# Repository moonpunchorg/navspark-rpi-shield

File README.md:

# NavSpark Shield for Raspberry Pi

[NavSpark][NavSpark] is Arduino compatible microcontroller board that has built in satellite navigation ([GPS][GPS] by default, and some models add [GLONASS][GLONASS], [BeiDou][BeiDou], etc...).

This adapter board provides means to connect the NavSpark board to a Raspberry Pi / Raspberry Pi 2.

For one example usecase, could create [a local network NTP server with accurate statellite timing through GPS+1PPS][timing]

## Files

This repository contains the design files using [KiCad 4.0][kicad]. The appropriate directories also contain the Gerber files, ready to be manufactured.

A note for those using [Seeed's FusionPCB service][fusionpcb]: the edge cuts filename needs to be changed from `*.gm1` to `*.gml`, and the drill file from `*.drl` to `.txt`.

## PCB

Revision v1, the proof of concept looks like this:

![PCB Front][pcbfront]

![PCB Back][pcbback]

[NavSpark]: http://www.navspark.com.tw/ "NavSpark homepage"
[GPS]: https://en.wikipedia.org/wiki/Global_Positioning_System "GPS on Wikipedia"
[GLONASS]: https://en.wikipedia.org/wiki/Global_Positioning_System "GLONASS on Wikipedia"
[BeiDou]: https://en.wikipedia.org/wiki/BeiDou_Navigation_Satellite_System "BeiDou on Wikipedia"
[timing]: https://gergely.imreh.net/blog/2015/11/navspark-beidou-ntp/ "Dual Satellite NTP server with Navspark"
[kicad]: http://kicad.org/ "KiCad homepage"
[fusionpcb]: https://www.seeedstudio.com/service/index.php?r=pcb "Seeed Studio FusionPCB"

[pcbfront]: ./images/navspark_rpi_shield_v1_front.png "PCB front rendering with Kicad"
[pcbback]: ./images/navspark_rpi_shield_v1_back.png "PCB back rendering with KiCad"

## License

Copyright 2015 Gergely Imreh <imrehg@gmail.com>

This documentation describes Open Hardware and is licensed under the
[CERN OHL v1.2](./LICENSE.txt).

You may redistribute and modify this documentation under the terms of the
CERN OHL v.1.2. (http://ohwr.org/cernohl). This documentation is distributed
WITHOUT ANY EXPRESS OR IMPLIED WARRANTY, INCLUDING OF MERCHANTABILITY,
SATISFACTORY QUALITY AND FITNESS FOR A PARTICULAR PURPOSE.
Please see the CERN OHL v.1.2 for applicable conditions.

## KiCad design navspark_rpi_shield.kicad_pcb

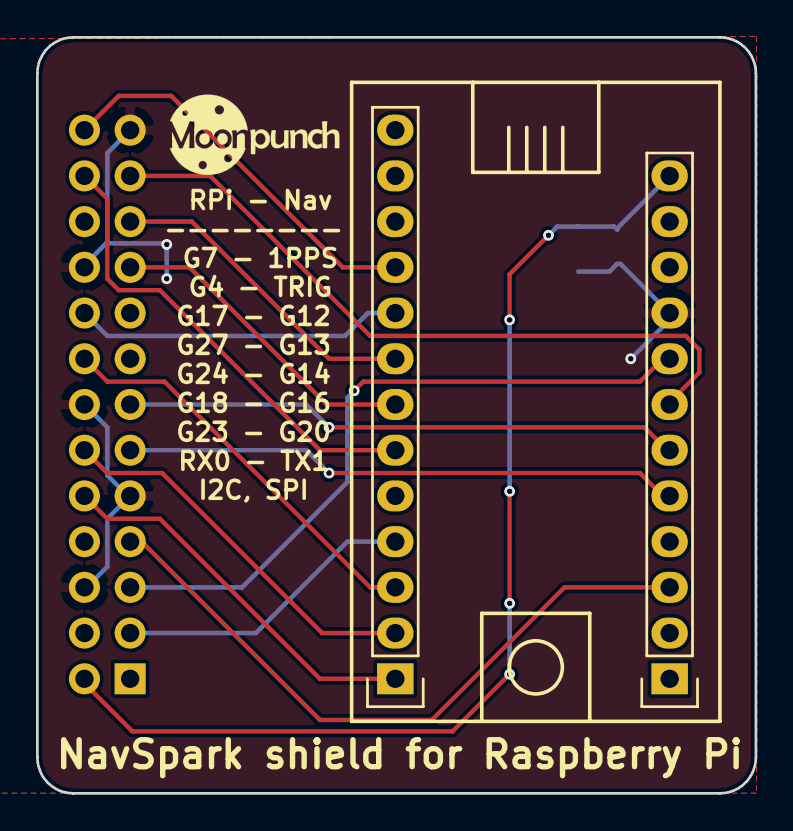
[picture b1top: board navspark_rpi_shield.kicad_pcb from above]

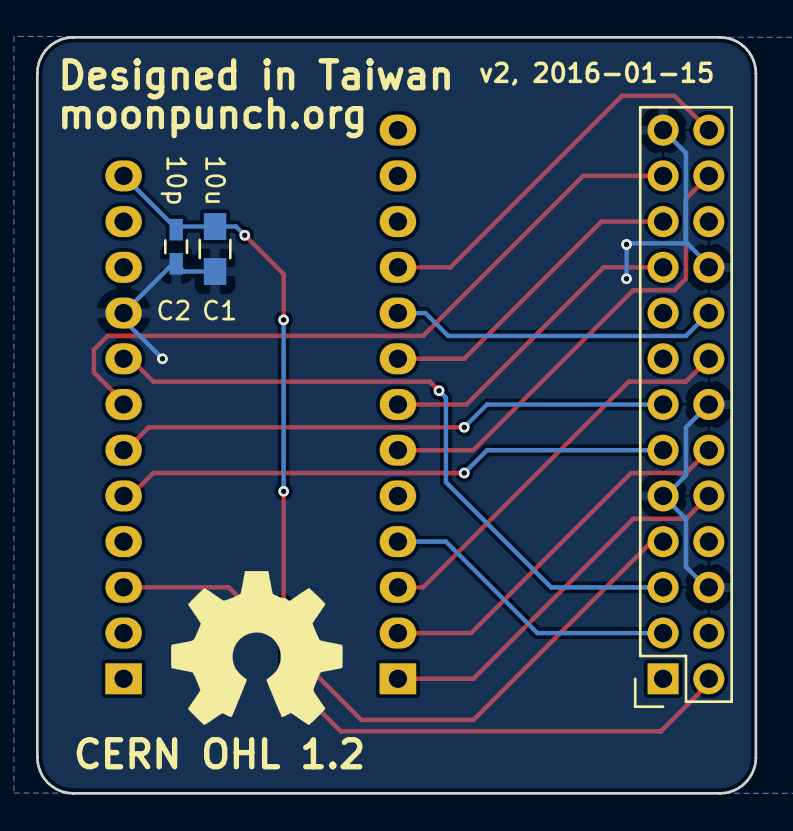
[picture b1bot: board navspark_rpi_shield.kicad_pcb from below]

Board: 2 copper layers, 39.9 x 42.0 mm, 5 parts (3 on the bottom side), 16 nets.

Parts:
C1: 10u; C_0805_HandSoldering
C2: 10p; C_0603_HandSoldering
P1: RPI_02X13; Socket_Strip_Straight_2x13
P2: NAV_01X13; Socket_Strip_Straight_1x13
P3: NAV_01X12; Socket_Strip_Straight_1x12

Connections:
/1PPS: P1.26, P2.10
/GPIO12: P1.11, P3.5
/GPIO13: P1.13, P3.6
/GPIO14: P1.18, P2.9
/GPIO16: P1.12, P2.2
/GPIO20: P1.16, P2.3
/I2C_SCL: P1.5, P3.8
/I2C_SDA: P1.3, P2.4
/N_TXD1: P1.10, P2.1
/SPI_CSN0: P1.24, P2.6
/SPI_MISO: P1.21, P2.8
/SPI_MOSI: P1.19, P2.7
/SPI_SCK: P1.23, P3.7
/TRIG: P1.7, P3.3
GND: C1.2, C2.2, P1.6, P1.9, P1.14, P1.20, P1.25, P3.9
VCC: C1.1, C2.1, P1.2, P3.12

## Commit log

2015-12-20 work in progress
2015-12-20 add .gitignore
2015-12-20 small changes
2015-12-20 remove spurious whitespace
2015-12-21 save changes before submission
2015-12-21 add gerbers
2015-12-21 add license and readme
2015-12-21 fix typos in readme
2015-12-21 add license to readme
2016-01-15 add v2 of the board
2021-11-10 Update README.md
    https://forum.kicad.info/t/warning-avoid-all-links-to-kicad-pcb-org-use-kicad-org/31521

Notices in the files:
README.md:
License: CERN OHL 1.2
navspark_rpi_shield.kicad_pcb:
CERN Open Hardware License 1.2
CERN OHL 1.2
